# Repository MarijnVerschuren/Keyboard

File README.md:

# Keyboard
Custom keyboard PCB featuring the STM32F412

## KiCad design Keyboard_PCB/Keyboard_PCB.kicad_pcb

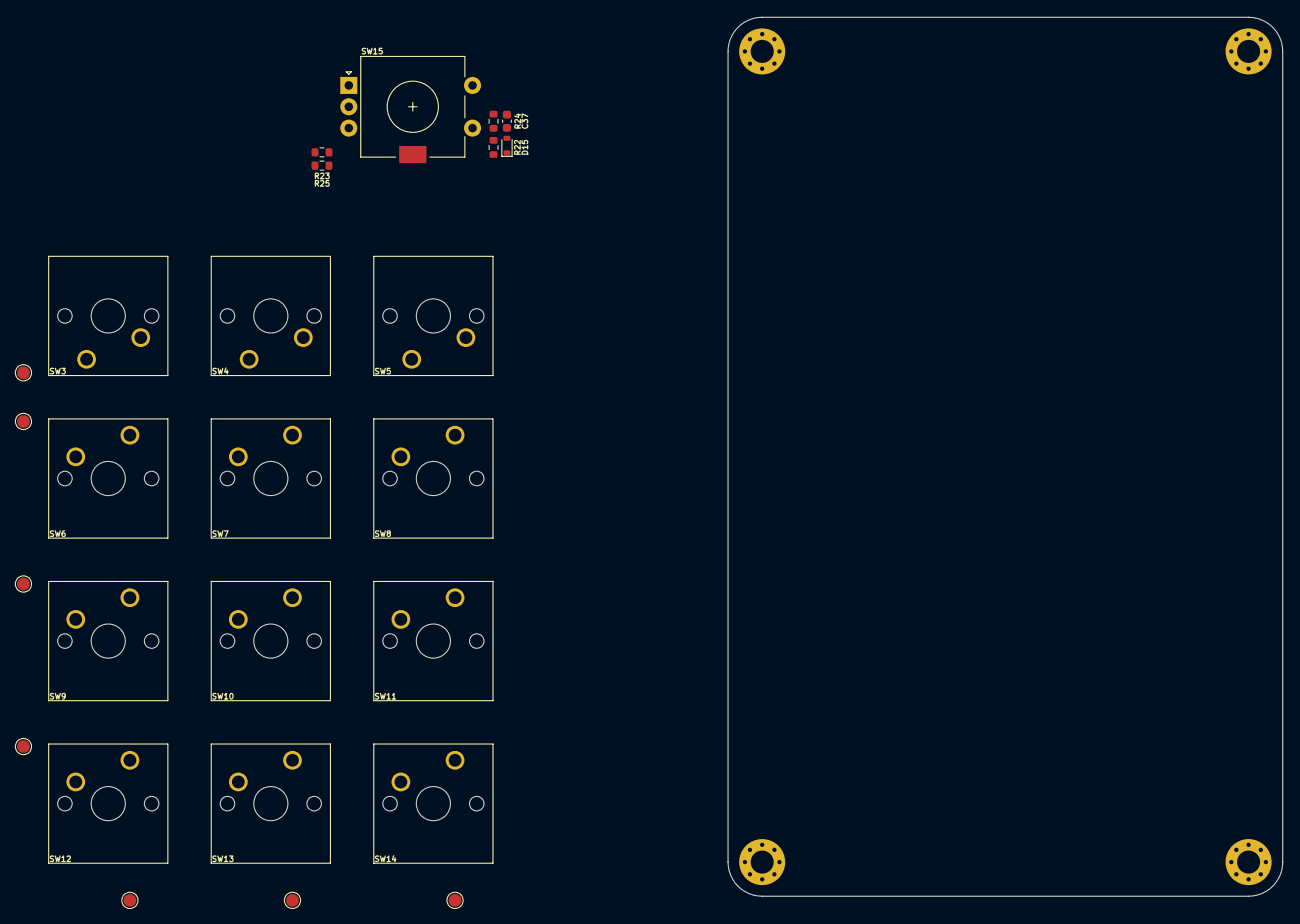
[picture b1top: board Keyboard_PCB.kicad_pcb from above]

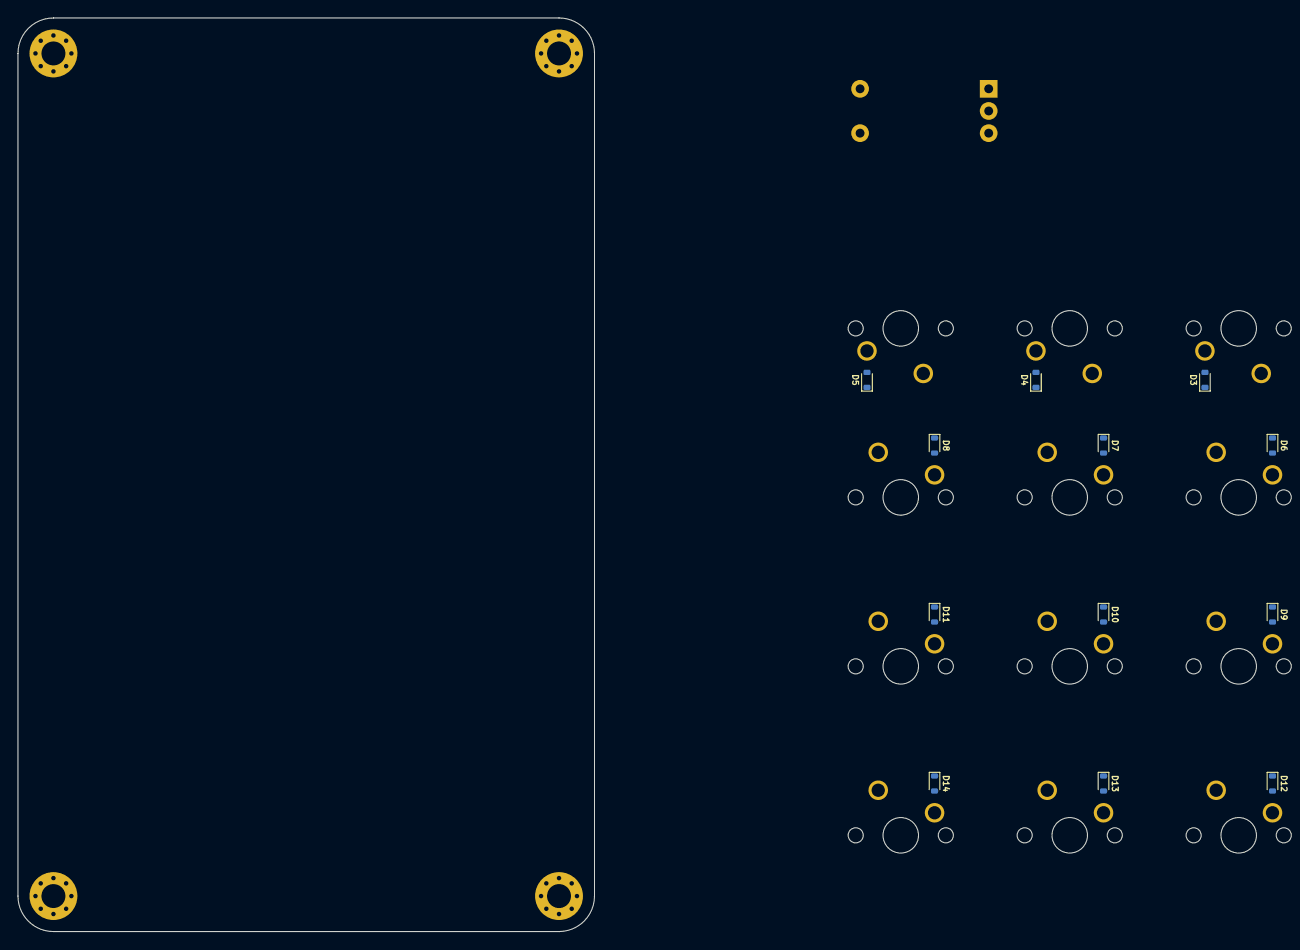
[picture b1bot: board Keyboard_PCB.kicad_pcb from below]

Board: 6 copper layers, 65.0 x 103.0 mm, 42 parts (12 on the bottom side), 25 nets, no tracks yet.

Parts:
C37: 100n; C_0603_1608Metric
D3, D4, D5, D6, D7, D8, D9, D10, D11, D12, D13, D14, D15: SOD-523F
H1, H2, H3, H4: MountingHole_Pad; MountingHole_2.7mm_M2.5_Pad_Via
R22, R23, R24, R25: 10k; R_0603_1608Metric
SW3: 0; SW_Cherry_MX_1.00u_PCB
SW4: 1; SW_Cherry_MX_1.00u_PCB
SW5: 2; SW_Cherry_MX_1.00u_PCB
SW6: 3; SW_Cherry_MX_1.00u_PCB
SW7: 4; SW_Cherry_MX_1.00u_PCB
SW8: 5; SW_Cherry_MX_1.00u_PCB
SW9: 6; SW_Cherry_MX_1.00u_PCB
SW10: 7; SW_Cherry_MX_1.00u_PCB
SW11: 8; SW_Cherry_MX_1.00u_PCB
SW12: 9; SW_Cherry_MX_1.00u_PCB
SW13: 10; SW_Cherry_MX_1.00u_PCB
SW14: 11; SW_Cherry_MX_1.00u_PCB
SW15: EC11E15244G1; EC11E_rotary_MP_pads
TP1: COL0; TestPoint_Pad_D1.5mm
TP2: COL1; TestPoint_Pad_D1.5mm
TP3: COL2; TestPoint_Pad_D1.5mm
TP4: ROW0; TestPoint_Pad_D1.5mm
TP5: ROW1; TestPoint_Pad_D1.5mm
TP6: ROW2; TestPoint_Pad_D1.5mm
TP7: ROW3; TestPoint_Pad_D1.5mm

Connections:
+3V3: R22.1, R23.1, R25.1
/COL_0: SW3.1, SW6.1, SW9.1, SW12.1, TP1.1
/COL_1: SW4.1, SW7.1, SW10.1, SW13.1, TP2.1
/COL_2: SW5.1, SW8.1, SW11.1, SW14.1, TP3.1
/ROT_A: R23.2, SW15.A
/ROT_B: R25.2, SW15.B
/ROT_SW: C37.1, D15.1 (K), R24.1
/ROW_0: D3.1 (K), D4.1 (K), D5.1 (K), TP4.1
/ROW_1: D6.1 (K), D7.1 (K), D8.1 (K), TP5.1
/ROW_2: D9.1 (K), D10.1 (K), D11.1 (K), TP6.1
/ROW_3: D12.1 (K), D13.1 (K), D14.1 (K), TP7.1
GND: C37.2, H1.1, H2.1, H3.1, H4.1, SW15.C, SW15.S2
unnamed: D3.2 (A), SW3.2
unnamed: D4.2 (A), SW4.2
unnamed: D5.2 (A), SW5.2
unnamed: D6.2 (A), SW6.2
unnamed: D7.2 (A), SW7.2
unnamed: D8.2 (A), SW8.2
unnamed: D9.2 (A), SW9.2
unnamed: D10.2 (A), SW10.2
unnamed: D11.2 (A), SW11.2
unnamed: D12.2 (A), SW12.2
unnamed: D13.2 (A), SW13.2
unnamed: D14.2 (A), SW14.2
unnamed: D15.2 (A), R22.2, R24.2, SW15.S1

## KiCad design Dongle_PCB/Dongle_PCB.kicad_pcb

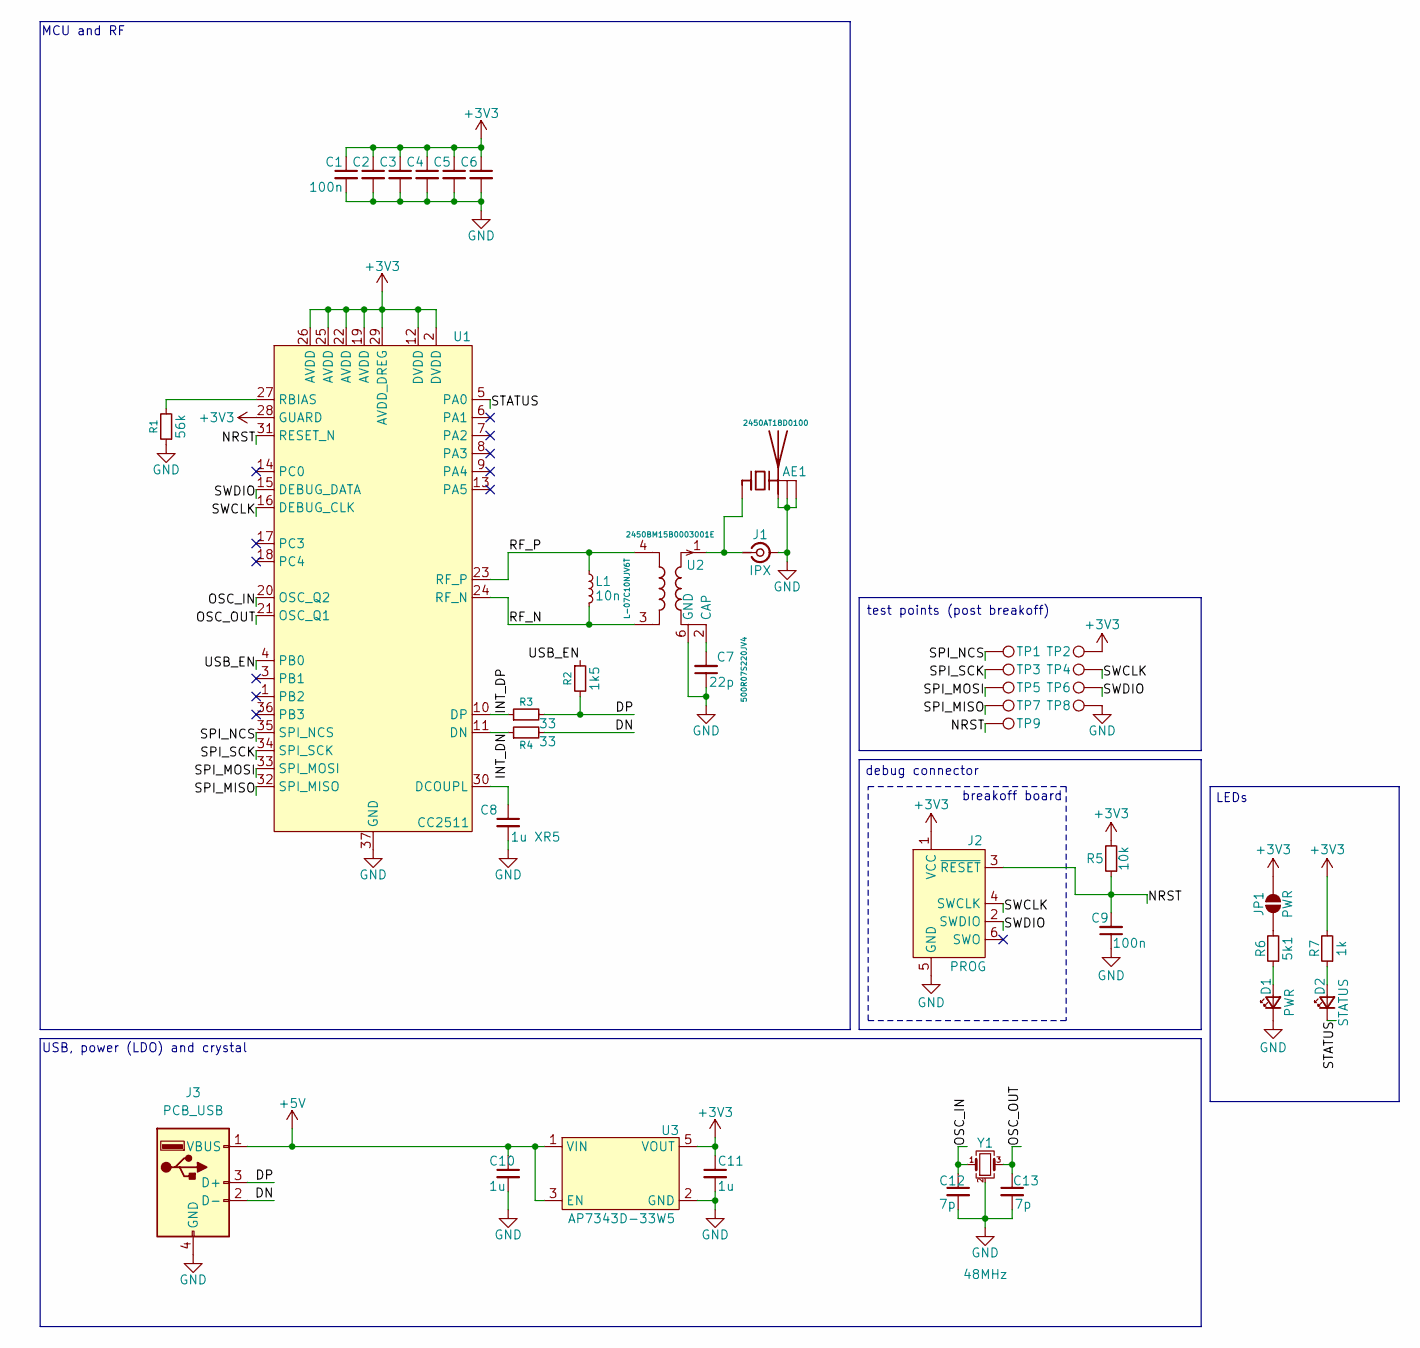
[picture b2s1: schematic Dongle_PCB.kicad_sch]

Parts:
AE1: 2450AT18D0100; mouser 609-2450AT18D0100001
C1, C2, C3, C4, C5, C6, C9: 100n; C_0603_1608Metric
C7: 22p; C_0603_1608Metric
C8: 1u XR5; C_0603_1608Metric
C10, C11: 1u; C_0603_1608Metric
C12, C13: 7p; C_0603_1608Metric
D1: PWR; LED_0603_1608Metric; mouser 710-150060AS75000
D2: STATUS; LED_0603_1608Metric; mouser 710-150060AS75000
J1: IPX; U.FL_Molex_MCRF_73412-0110_Vertical
J2: PROG; Tag-Connect_TC2030-IDC-FP_2x03_P1.27mm_Vertical
J3: PCB_USB
JP1: PWR; SolderJumper-2_P1.3mm_Open_TrianglePad1.0x1.5mm
L1: 10n; L_0402_1005Metric; mouser 609-LRC0402CJ10NGV00
R1: 56k; R_0603_1608Metric
R2: 1k5; R_0603_1608Metric
R3, R4: 33; R_0603_1608Metric
R5: 10k; R_0603_1608Metric
R6: 5k1; R_0603_1608Metric
R7: 1k; R_0603_1608Metric
TP1, TP2, TP3, TP4, TP5, TP6, TP7, TP8, TP9: TestPoint; test_point_SMD_0.8mm
U1: CC2511; QFN-36-1EP_6x6mm_P0.5mm_EP4.1x4.1mm
U2: 2450BM15B0003001E; mouser 609-2450BM15B0003001
U3: AP7343D-33W5; SOT-25
Y1: 48MHz; Crystal_SMD_2016-4Pin_2.0x1.6mm; Mouser 815-FC1BSHHVK48.0-T3

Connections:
+3V3: C1.1, C2.1, C3.1, C4.1, C5.1, C6.1, C11.1, J2.1 (VCC), JP1.2 (B), R5.2, R7.2, TP2.1, U1.2 (DVDD), U1.12 (DVDD), U1.19 (AVDD), U1.22 (AVDD), U1.25 (AVDD), U1.26 (AVDD), U1.28 (GUARD), U1.29 (AVDD_DREG), U3.5 (VOUT)
+5V: C10.1, J3.1 (VBUS), U3.1 (VIN), U3.3 (EN)
/DN: J3.2 (D-), R4.2
/DP: J3.3 (D+), R2.2, R3.2
/INT_DN: R4.1, U1.11 (DN)
/INT_DP: R3.1, U1.10 (DP)
/NRST: C9.2, J2.3 (~RESET), R5.1, TP9.1, U1.31 (RESET_N)
/OSC_IN: C12.1, U1.20 (OSC_Q2), Y1.1
/OSC_OUT: C13.1, U1.21 (OSC_Q1), Y1.3
/RF_N: L1.2, U1.24 (RF_N), U2.3
/RF_P: L1.1, U1.23 (RF_P), U2.4
/SPI_MISO: TP7.1, U1.32 (SPI_MISO)
/SPI_MOSI: TP5.1, U1.33 (SPI_MOSI)
/SPI_NCS: TP1.1, U1.35 (SPI_NCS)
/SPI_SCK: TP3.1, U1.34 (SPI_SCK)
/STATUS: D2.1 (K), U1.5 (PA0)
/SWCLK: J2.4 (SWCLK), TP4.1, U1.16 (DEBUG_CLK)
/SWDIO: J2.2 (SWDIO), TP6.1, U1.15 (DEBUG_DATA)
/USB_EN: R2.1, U1.4 (PB0)
GND: AE1.2, AE1.3, AE1.4, C1.2, C2.2, C3.2, C4.2, C5.2, C6.2, C7.1, C8.2, C9.1, C10.2, C11.2, C12.2, C13.2, D1.1 (K), J1.2 (Ext), J2.5 (GND), J3.4 (GND), R1.1, TP8.1, U1.37 (GND), U2.5 (GND), U2.6 (GND), U3.2 (GND), Y1.2 (G), Y1.4 (G)
unnamed: AE1.1 (FEED), J1.1 (In), U2.1
unnamed: D1.2 (A), R6.1
unnamed: D2.2 (A), R7.1
unnamed: JP1.1 (A), R6.2
unnamed: C8.1, U1.30 (DCOUPL)
unnamed: R1.2, U1.27 (RBIAS)
unnamed: C7.2, U2.2 (CAP)

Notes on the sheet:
USB, power (LDO) and crystal
test points (post breakoff)
LEDs
debug connector
breakoff board
MCU and RF

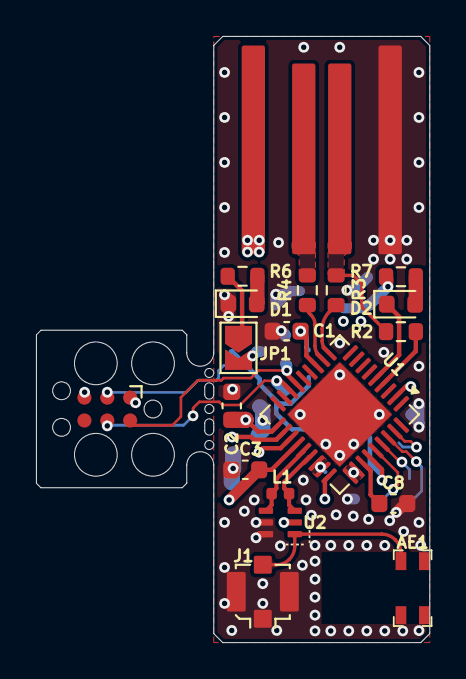
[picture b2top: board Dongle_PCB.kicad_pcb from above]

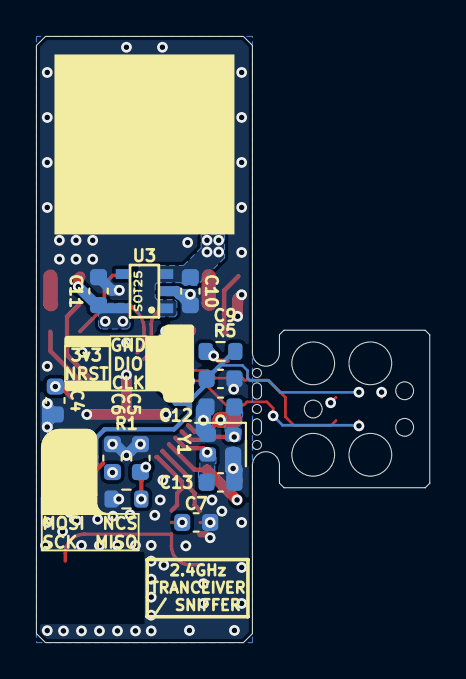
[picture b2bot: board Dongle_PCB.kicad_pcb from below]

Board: 4 copper layers, 21.8 x 33.7 mm, 41 parts (22 on the bottom side), 27 nets.

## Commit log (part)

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2023-06-24 Added STM32H library to the software folder
2024-04-16 Changed board to STM32H7B0
2024-04-16 Updated update.sh
2024-04-16 Removed bugged software source folder
2024-04-16 Send text loaded from encrypted ROM as keyboard!!!
2024-04-18 password ROM init
2024-04-18 add_password working!
2024-04-18 Read desciptor / password
2024-04-19 Read descriptor / password working!
2024-04-19 STM32H7B0_CMSIS update
2024-05-18 Created KiCad project
2024-05-18 Schematic V1
2024-05-19 65% PCB layout!
2024-05-19 Rough Layout
2024-05-19 Layout Progress
    Layout is finished except for the buck converter
2024-05-19 Layout Progress
2024-05-19 Added TODO's
2024-05-20 Layout V1
2024-05-20 Final layout
2024-05-20 Added TODOs
2024-05-21 Filled in signal layers for copper balancing
2024-05-22 Fixed errors in BOM file
2024-05-22 Found error in BOM
2024-05-23 Removed TODO
2024-05-29 Finished design V0
2024-05-29 75% keyboard layout test
2024-05-30 Empty 65% key grid
2024-05-30 LCD-overhead test
2024-05-30 USB placement
2024-06-04 Finished Layout V1
2024-06-04 Bugfix
2024-06-05 Added battery charging support
2024-06-27 Key scanning
2024-06-30 STM32H7B0_CMSIS updates, started on LCD, W25Q128
2024-07-01 config.h
    LCD does not work :(
2024-08-08 Changed the way key reporting works
    TODO: debug
2024-10-10 OLD version final commit
2024-10-10 Cleaned up project
2024-10-10 Added software
2024-10-11 Added STM32F412
2024-10-13 Power section progress
2024-10-14 Power section finished
2024-10-14 Progress
2024-10-14 Footprint assignments
    TODO: check FPC connector
2024-10-17 Power layout progress
2024-10-19 Battery charger layout done
2024-10-21 Buck layout progress
2024-10-21 Buck layout finished
2024-10-25 Layout V1.1 + gerbers
2024-10-25 Layout V1.2 + gerbers
    JLC_PCB QR code
2024-10-26 Cleanup
2024-11-27 Test board V1.2
2025-02-03 Keyboard V2 outline
2025-07-05 Updated gitignore
2025-07-05 Keypad schematic progress
2025-07-11 STM32U385 pin assignment progress
2025-07-11 Schematic done
2025-07-13 eMMC routing and STM passives
2025-07-13 Buck and bat routing
2025-08-03 RF layout progress
2025-08-04 Grid diode layout
2025-08-04 Layout first draft
    TODO: gnd stitching, check connections and schematic again
2025-08-04 Routing V1
2025-08-12 Added mouser IDs to components and checked STM-eMMC connection
2025-08-13 Added additional power filtering and improved RF path
2025-08-14 Improved battery sens and added JLCPCB QR code
2025-08-15 Added TODOs for next version
2025-08-15 Added active battery sensing circuit
2025-08-15 Added grid and GND testpoints
2025-08-20 Checked and fixed LCD
2026-03-16 Dongle and keyboard backup memory
